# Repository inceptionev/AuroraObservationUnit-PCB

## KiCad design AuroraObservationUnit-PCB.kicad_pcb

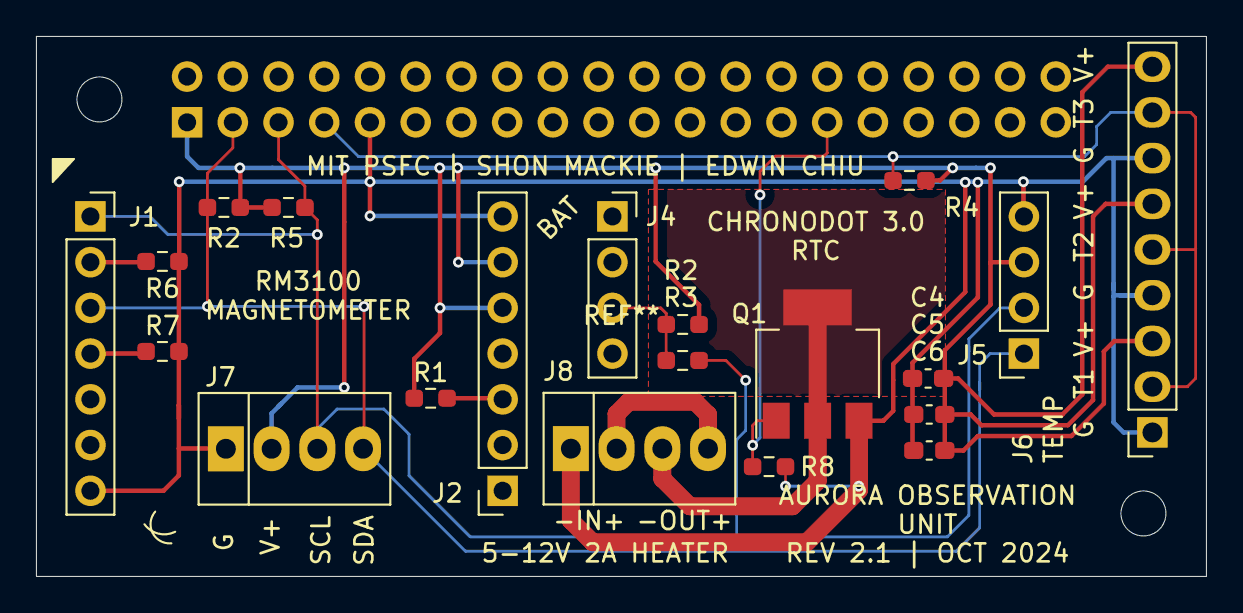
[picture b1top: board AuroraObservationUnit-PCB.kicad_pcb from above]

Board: 2 copper layers, 65.0 x 30.0 mm, 21 parts (1 on the bottom side), 12 nets.

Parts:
C4, C5, C6: 0.1uF; C_0603_1608Metric_Pad1.08x0.95mm_HandSolder
J1, J2: Conn_01x07_Female; PinSocket_1x07_P2.54mm_Vertical
J3: Raspberry_Pi_2_3; PinSocket_2x20_P2.54mm_Vertical
J4, J5: Conn_01x04_Female; PinSocket_1x04_P2.54mm_Vertical
J6: Conn_01x09_Female; 282834-9
J7, J8: Screw_Terminal_01x04; 1725672
Q1: STN4NF03L; SOT-223-3_TabPin2
R1, R2#2: 10k; R_0603_1608Metric_Pad0.98x0.95mm_HandSolder
R2, R4, R5, R8: 4k7; R_0603_1608Metric_Pad0.98x0.95mm_HandSolder
R3, R6, R7: 0; R_0603_1608Metric_Pad0.98x0.95mm_HandSolder

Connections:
+3V3: C4.1, C5.1, C6.1, J2.5, J2.6, J3.1, J5.3, J6.3, J6.6, J6.9, J7.2, R1.1, R2.1, R2#2.1, R4.1, R5.1
/DQ: J3.7, J6.2, J6.5, J6.8, R4.2
/HEATER+: J8.2, J8.4
/HEATER-: J8.3, Q1.2
/HEATER_CTRL: J3.29, Q1.1, R8.1
/I2C-EN: J2.3, R1.2
/SCL: J1.1, J3.5, J5.2, J7.3, R3.2, R5.2
/SDA: J1.3, J3.3, J5.1, J7.4, R2.2
/SQW: J4.3, R2#2.2, R3.1
GND: C4.2, C5.2, C6.2, J1.7, J2.7, J3.9, J5.4, J6.1, J6.4, J6.7, J7.1, J8.1, Q1.3, R6.2, R7.2, R8.2
unnamed: J1.2, R6.1
unnamed: J1.4, R7.1

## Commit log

2024-10-10 adding heater control, adding schematic and 3D step file
2024-10-10 manufacturing files
2024-10-17 adding thermos cage design
2024-10-18 adding slimmed down version for 40oz thermos, along with improvements in 0-ring sealing
2024-10-21 correction to silkscreen typo and regeneration of manufacturing package, now at rev 2.1
2025-02-20 adding hollow top version
2025-02-22 adding rev 2 design
